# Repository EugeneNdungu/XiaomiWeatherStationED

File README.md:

# Xiaomi Weather Station
This is a PCB design for a microclimate IoT system to be used to monitor temperature and relative humidity. The data will be collected from the Xiaomi BLE Temperature and Humidity sensor.

## Technologies
The system incorporates the following components:
* WeMos LOLIN32 V1.0.0 WiFi Bluetooth ESP-32 Based Board
* SIM800L GSM/GPRS Module 
* DS3231 RTC Module
* 16x2 LCD with I2C Module
* Micro SD Card Module
* LM2596 DC-DC Buck Converter Step-down Power Module

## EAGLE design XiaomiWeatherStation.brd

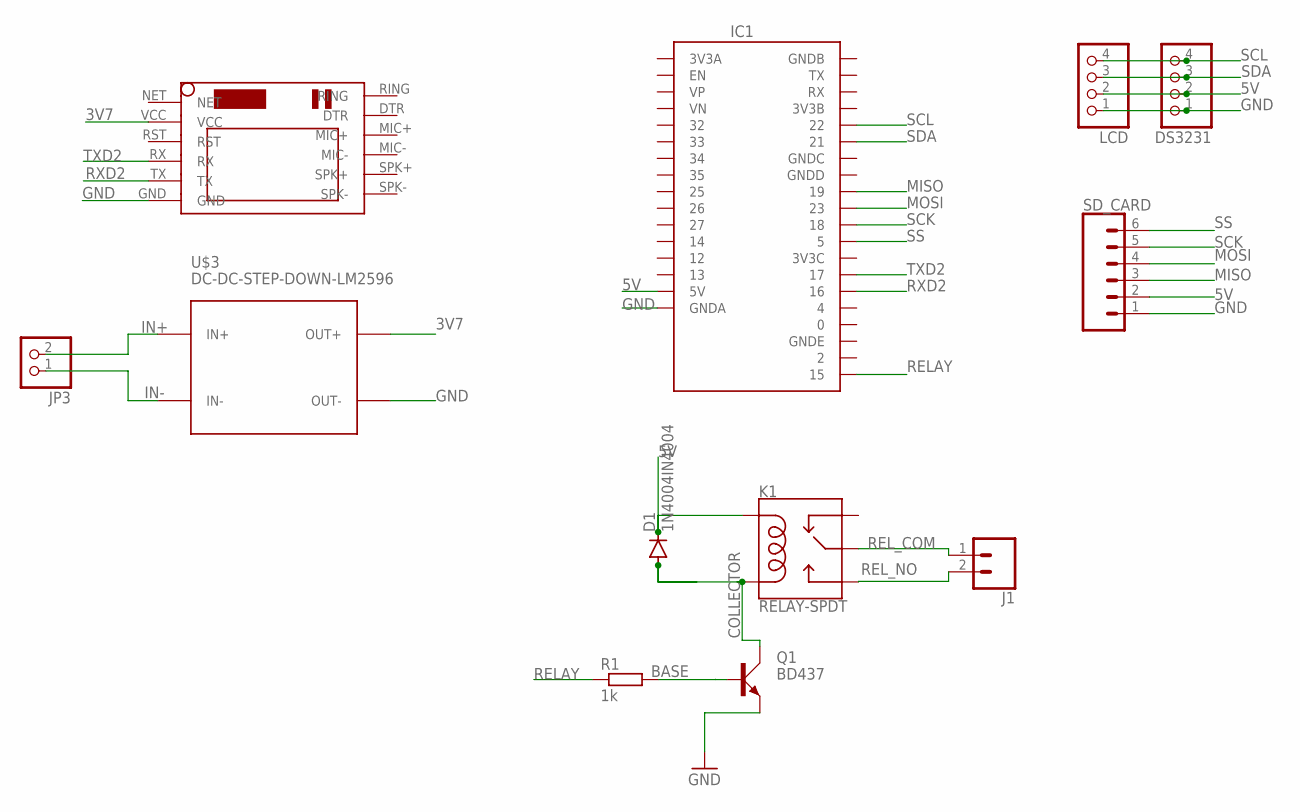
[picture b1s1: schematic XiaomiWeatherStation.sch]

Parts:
D1: 1N4004IN4004; DIOAD1176W63L850D250B
DS3231: PINHD-1X4; 1X04
IC1: SSFD_LOLIN32_WEMOS_CHINA_W_BATT
J1: CONN_025MM; SCREWTERMINAL-5MM-2
JP3: PINHD-1X2; 1X02
K1: RELAY-SPDT; RELAY_G5LE
LCD: PINHD-1X4; 1X04
Q1: BD437; TO126AV
R1: 1k; 0204/7
SD_CARD: CONN_06LONGPADS; 1X06_LONGPADS
U$1: SIM800LMODULE
U$3: DC-DC-STEP-DOWN-LM2596

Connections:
3V7: U$1.VCC, U$3.OUT+
5V: D1.1 (C), DS3231.2, IC1.5V, K1.2 (COIL1), LCD.2, SD_CARD.2
BASE: Q1.B, R1.2
COLLECTOR: D1.2 (A), K1.5 (COIL2), Q1.C
GND: DS3231.1, IC1.GNDA, LCD.1, Q1.E, SD_CARD.1, U$1.GND, U$3.OUT-
IN+: JP3.2, U$3.IN+
IN-: JP3.1, U$3.IN-
MISO: IC1.19, SD_CARD.3
MOSI: IC1.23, SD_CARD.4
RELAY: IC1.15, R1.1
REL_COM: J1.1, K1.1 (MAIN)
REL_NO: J1.2, K1.3 (NO)
RXD2: IC1.16, U$1.TX
SCK: IC1.18, SD_CARD.5
SCL: DS3231.4, IC1.22, LCD.4
SDA: DS3231.3, IC1.21, LCD.3
SS: IC1.5, SD_CARD.6
TXD2: IC1.17, U$1.RX

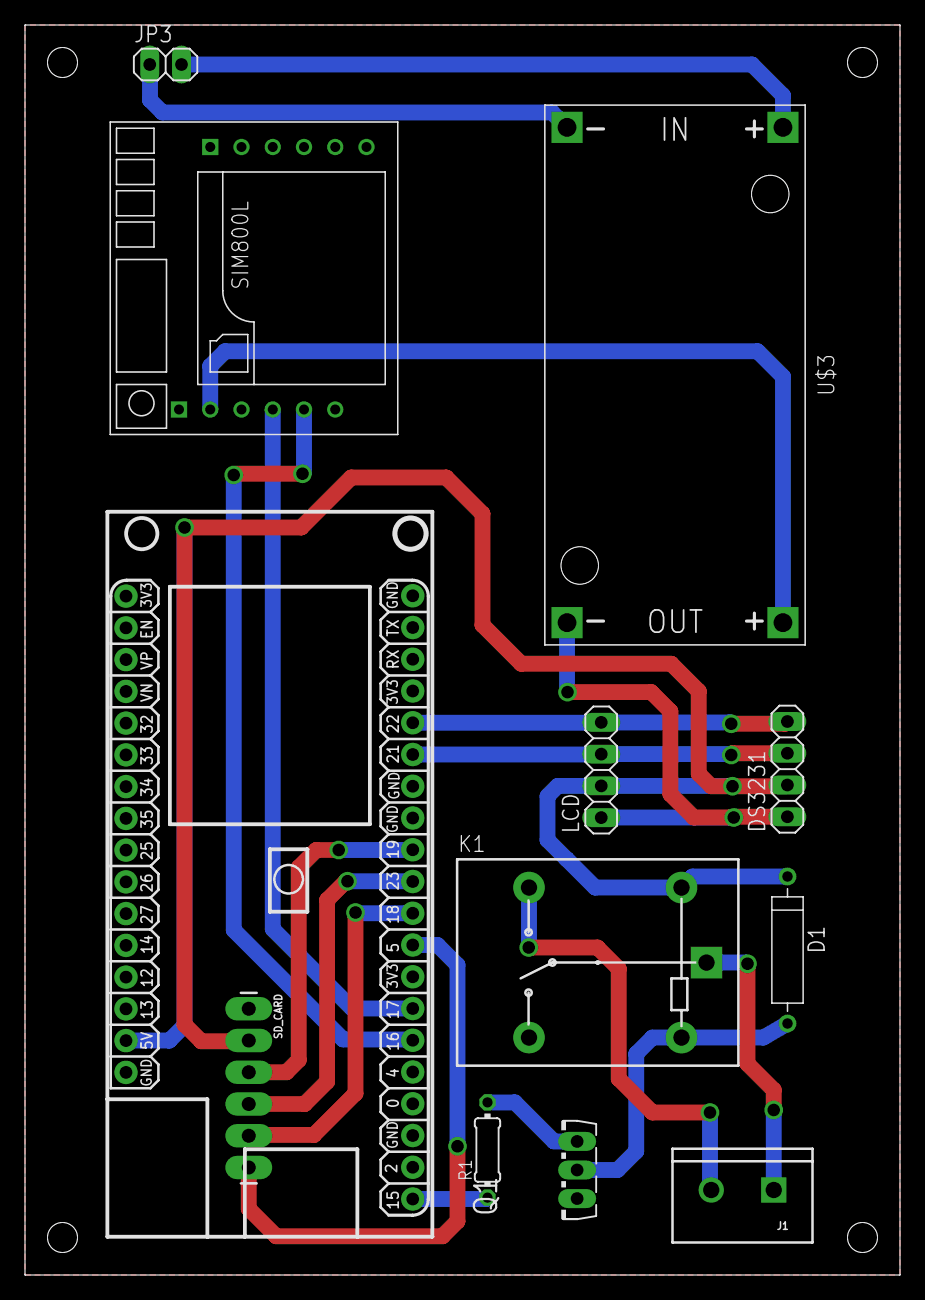
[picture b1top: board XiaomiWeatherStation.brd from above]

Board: 2 copper layers, 70.0 x 100.0 mm, 12 parts (0 on the bottom side), 18 nets.

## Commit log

2021-05-29 Adds .gitignore file
2021-05-29 Adds components to schematic file
2021-05-29 Finish routing
2021-05-29 Adds README file
2021-05-29 Adds information to the README file
2021-05-29 Adds external eagle libraries used in the design
2021-05-30 Adds relay to the schematic
2021-05-30 Adds relay to the pcb
2021-05-30 Completes routing
2021-10-10 moves the files to one folder
2021-10-18 Adds 3d packages to the components
2021-10-18 Adds actual sd and ds3231 components in place of header pins
2021-10-18 Completes design
2021-10-24 Changes the terminal block from 3.5mm to 5mm
2021-10-24 Adds ground plane
2021-10-24 Adds mounting holes(2.4mm)
2021-11-09 adds 3d models
2021-11-11 Updated to ignore zip files'

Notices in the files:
parts and their libraries:
diy-modules: Released under the Creative Commons Attribution 4.0 International License: http://creativecommons.org/licenses/by/4.0
SparkFun-Electromechanical: Licensing: Creative Commons ShareAlike 4.0 International - https://creativecommons.org/licenses/by-sa/4.0
